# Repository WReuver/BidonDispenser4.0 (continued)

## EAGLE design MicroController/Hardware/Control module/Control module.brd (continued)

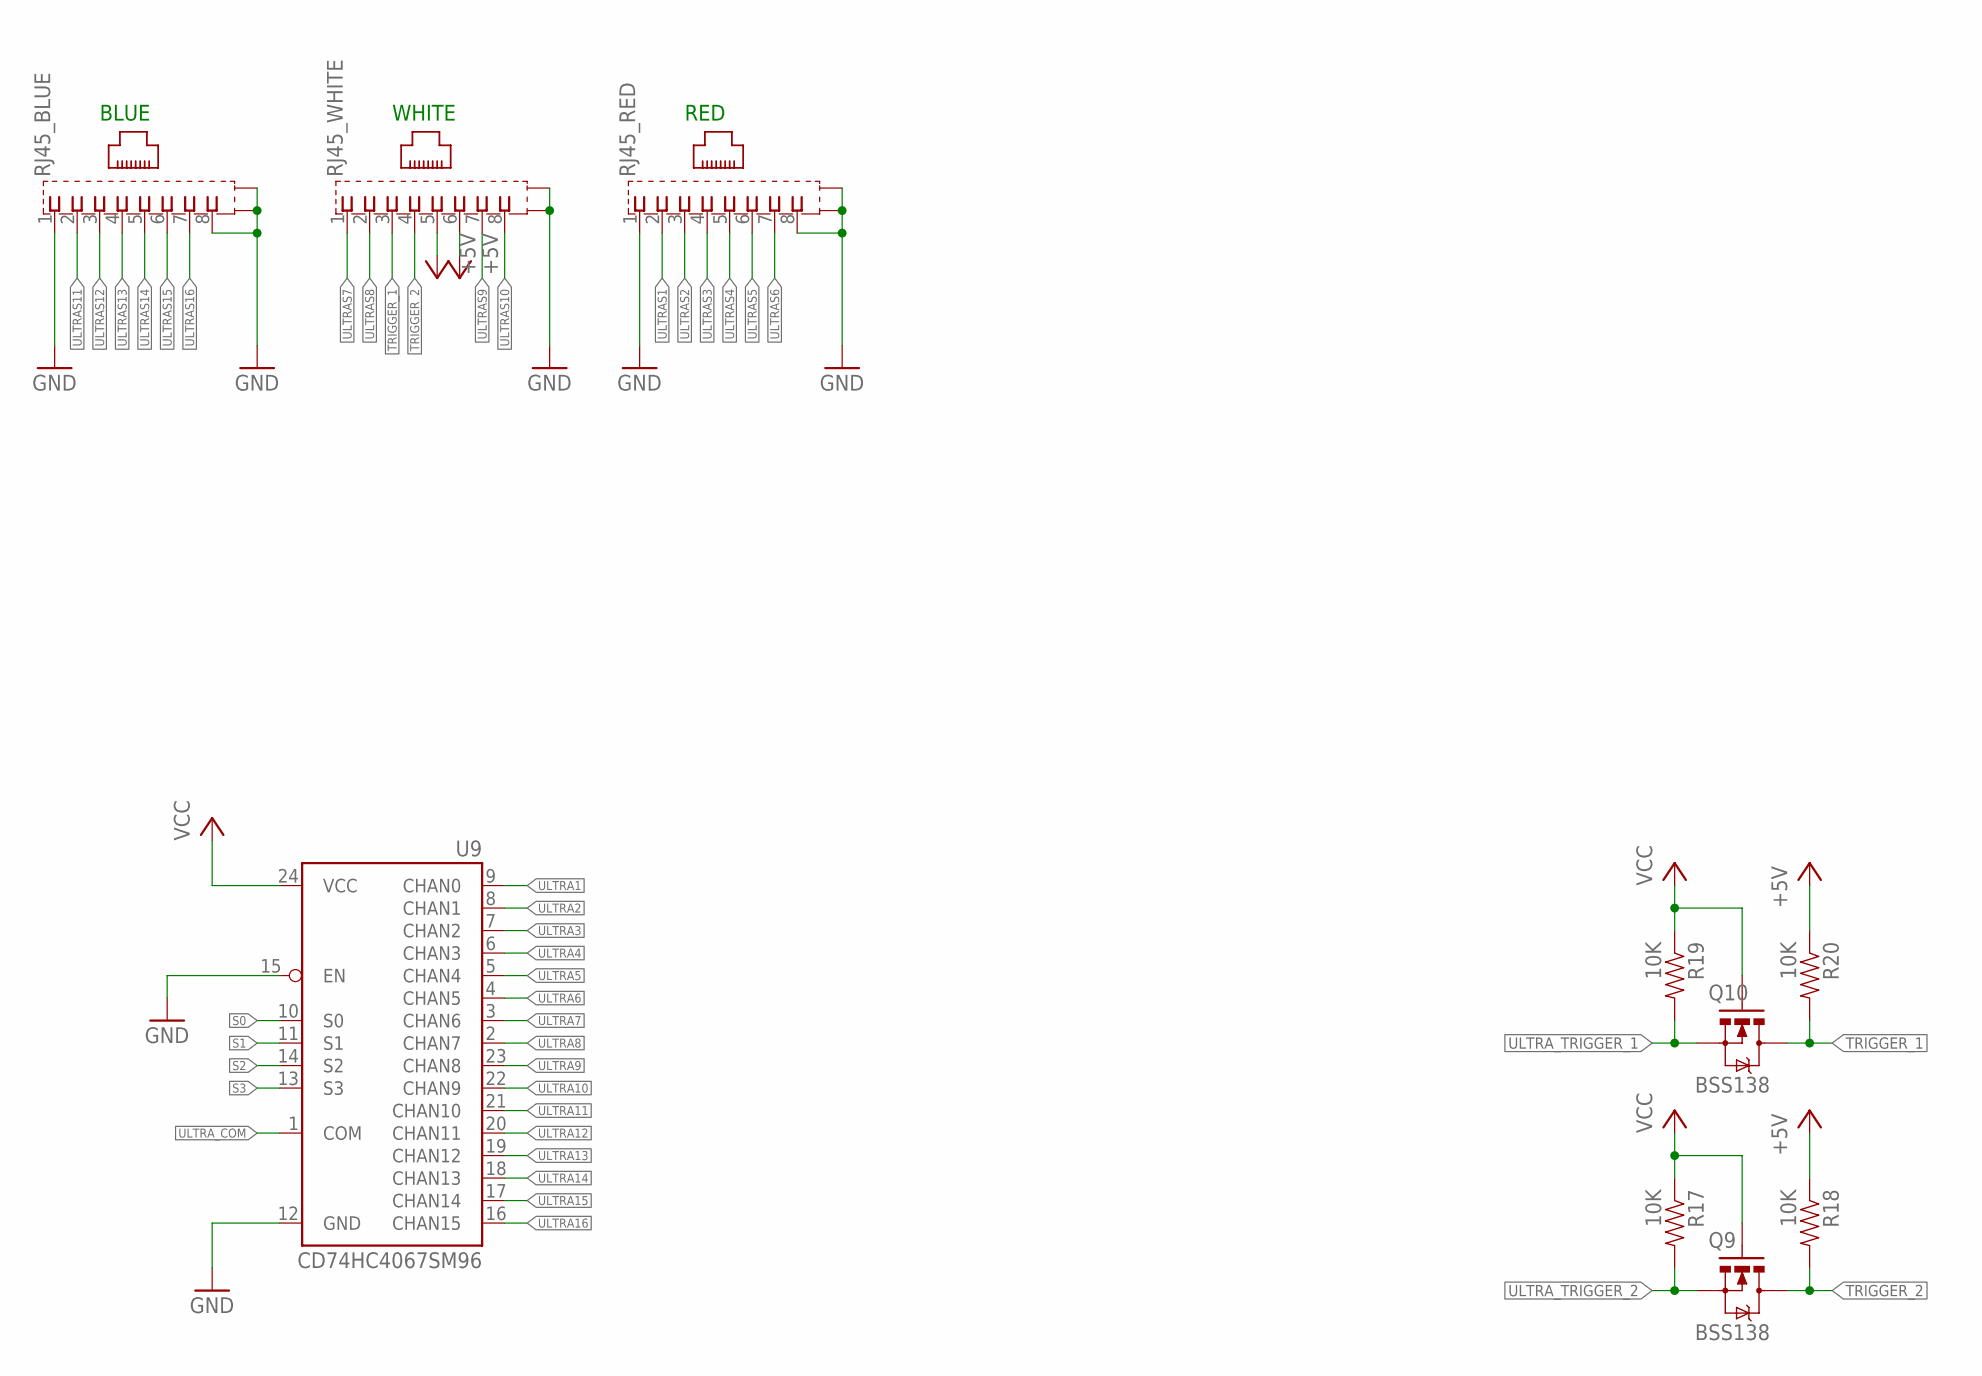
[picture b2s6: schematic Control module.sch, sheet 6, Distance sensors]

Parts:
Q9, Q10: BSS138; SOT23-3
R17, R18, R19, R20: 10K; 0603-RES
RJ45_BLUE, RJ45_RED, RJ45_WHITE: 0446200002
U9: CD74HC4067SM96; SSOP24

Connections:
+5V: R18.1, R20.1, RJ45_WHITE.5, RJ45_WHITE.6; also elsewhere on the board
GND: RJ45_BLUE.1, RJ45_BLUE.8, RJ45_BLUE.S@1 (S1), RJ45_BLUE.S@2 (S2), RJ45_RED.1, RJ45_RED.8, RJ45_RED.S@1 (S1), RJ45_RED.S@2 (S2), RJ45_WHITE.S@1 (S1), RJ45_WHITE.S@2 (S2), U9.12 (GND), U9.15 (EN); also elsewhere on the board
S0: U9.10 (S0); also elsewhere on the board
S1: U9.11 (S1); also elsewhere on the board
S2: U9.14 (S2); also elsewhere on the board
S3: U9.13 (S3); also elsewhere on the board
TRIGGER_1: Q10.3 (D), R20.2, RJ45_WHITE.3
TRIGGER_2: Q9.3 (D), R18.2, RJ45_WHITE.4
ULTRA1: U9.9 (CHAN0); also elsewhere on the board
ULTRA2: U9.8 (CHAN1); also elsewhere on the board
ULTRA3: U9.7 (CHAN2); also elsewhere on the board
ULTRA4: U9.6 (CHAN3); also elsewhere on the board
ULTRA5: U9.5 (CHAN4); also elsewhere on the board
ULTRA6: U9.4 (CHAN5); also elsewhere on the board
ULTRA7: U9.3 (CHAN6); also elsewhere on the board
ULTRA8: U9.2 (CHAN7); also elsewhere on the board
ULTRA9: U9.23 (CHAN8); also elsewhere on the board
ULTRA10: U9.22 (CHAN9); also elsewhere on the board
ULTRA11: U9.21 (CHAN10); also elsewhere on the board
ULTRA12: U9.20 (CHAN11); also elsewhere on the board
ULTRA13: U9.19 (CHAN12); also elsewhere on the board
ULTRA14: U9.18 (CHAN13); also elsewhere on the board
ULTRA15: U9.17 (CHAN14); also elsewhere on the board
ULTRA16: U9.16 (CHAN15); also elsewhere on the board
ULTRAS1: RJ45_RED.2; also elsewhere on the board
ULTRAS2: RJ45_RED.3; also elsewhere on the board
ULTRAS3: RJ45_RED.4; also elsewhere on the board
ULTRAS4: RJ45_RED.5; also elsewhere on the board
ULTRAS5: RJ45_RED.6; also elsewhere on the board
ULTRAS6: RJ45_RED.7; also elsewhere on the board
ULTRAS7: RJ45_WHITE.1; also elsewhere on the board
ULTRAS8: RJ45_WHITE.2; also elsewhere on the board
ULTRAS9: RJ45_WHITE.7; also elsewhere on the board
ULTRAS10: RJ45_WHITE.8; also elsewhere on the board
ULTRAS11: RJ45_BLUE.2; also elsewhere on the board
ULTRAS12: RJ45_BLUE.3; also elsewhere on the board
ULTRAS13: RJ45_BLUE.4; also elsewhere on the board
ULTRAS14: RJ45_BLUE.5; also elsewhere on the board
ULTRAS15: RJ45_BLUE.6; also elsewhere on the board
ULTRAS16: RJ45_BLUE.7; also elsewhere on the board
ULTRA_COM: U9.1 (COM); also elsewhere on the board
ULTRA_TRIGGER_1: Q10.2 (S), R19.2; also elsewhere on the board
ULTRA_TRIGGER_2: Q9.2 (S), R17.2; also elsewhere on the board
VCC: Q9.1 (G), Q10.1 (G), R17.1, R19.1, U9.24 (VCC); also elsewhere on the board

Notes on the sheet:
BLUE
WHITE
RED

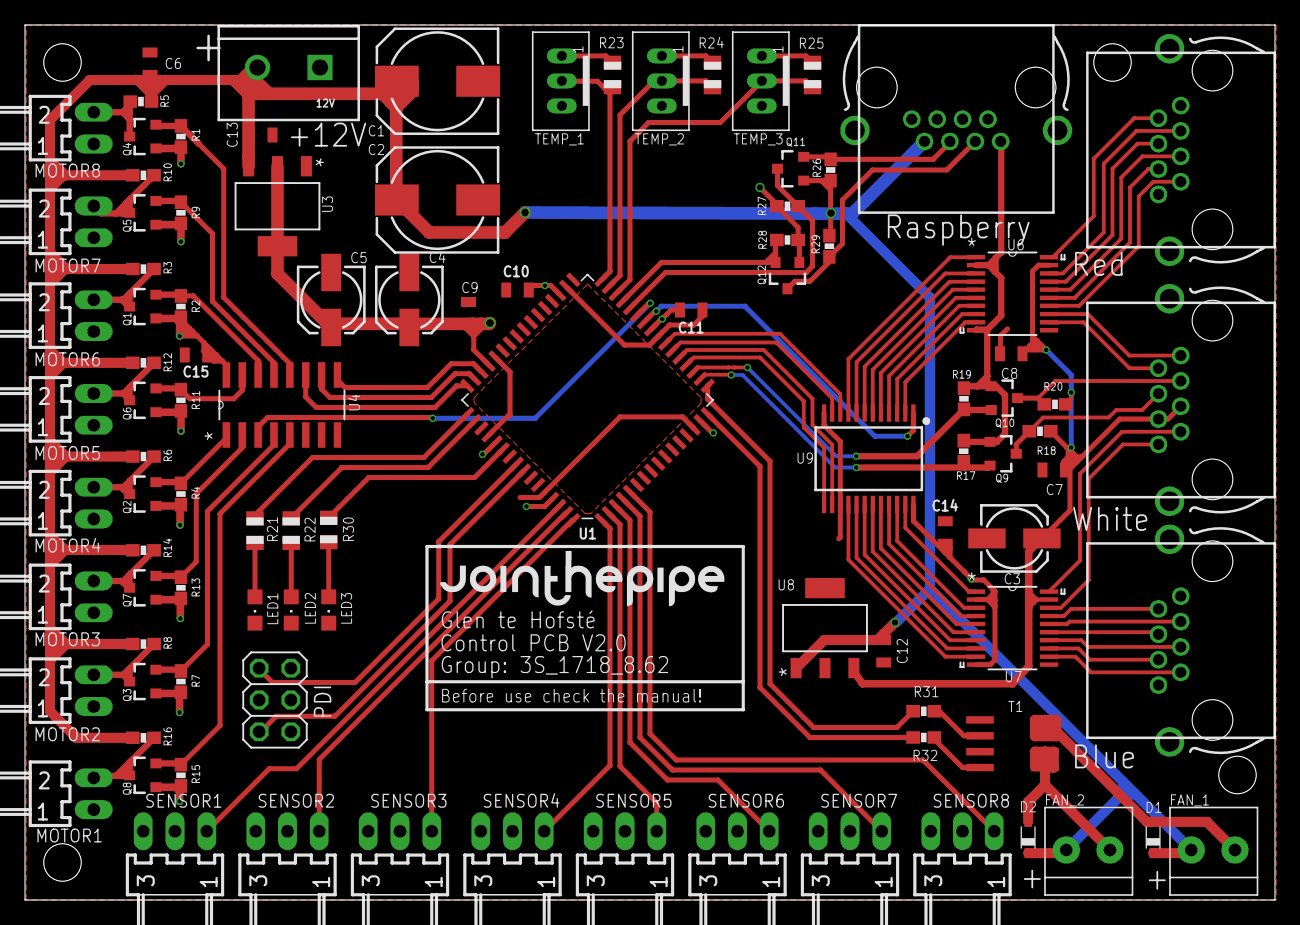
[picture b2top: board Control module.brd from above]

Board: 2 copper layers, 100.0 x 70.0 mm, 99 parts (0 on the bottom side), 94 nets.

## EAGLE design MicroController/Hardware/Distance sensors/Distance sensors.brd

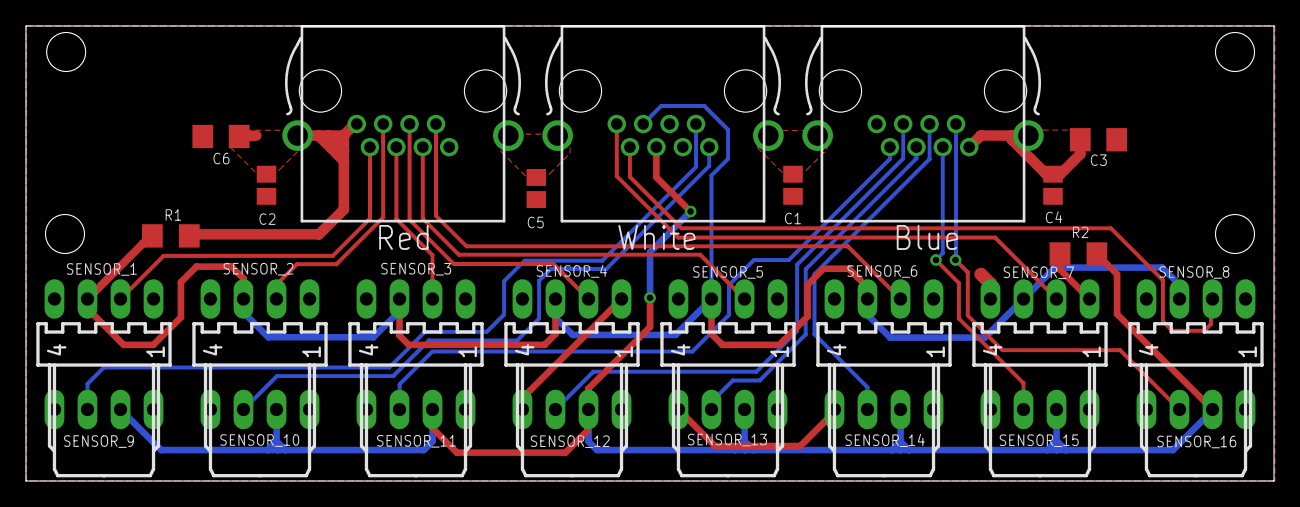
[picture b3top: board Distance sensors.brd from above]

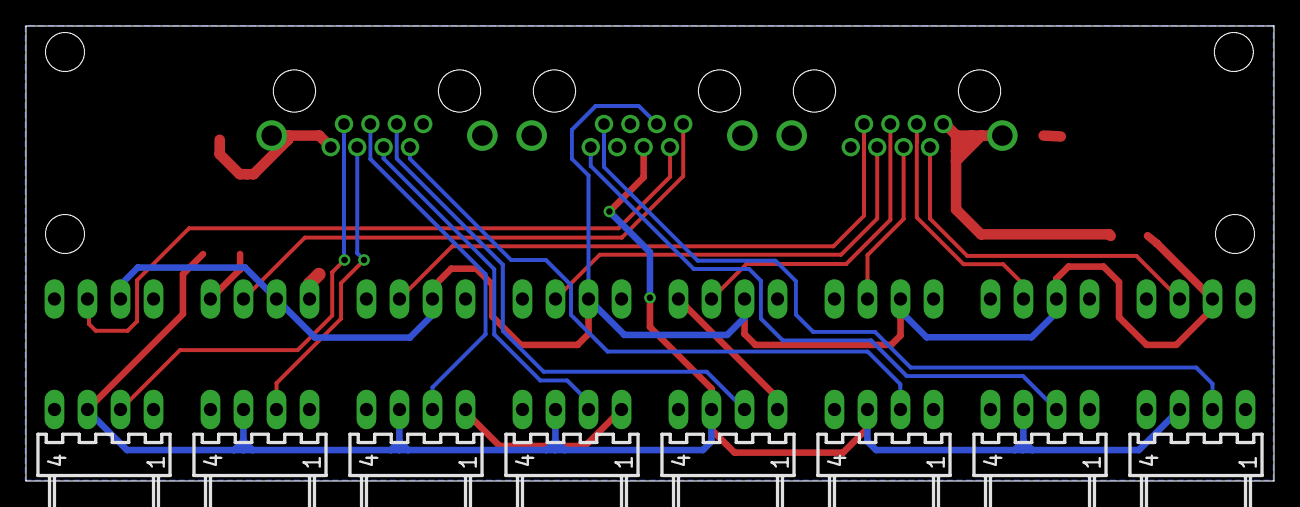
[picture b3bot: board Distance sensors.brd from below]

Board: 2 copper layers, 96.0 x 35.0 mm, 27 parts (8 on the bottom side), 20 nets.

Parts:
C1, C2, C4, C5: C0805
C3, C6: C1206
R1, R2: R1206
SENSOR_1, SENSOR_2, SENSOR_3, SENSOR_4, SENSOR_5, SENSOR_6, SENSOR_7, SENSOR_8, SENSOR_9, SENSOR_10, SENSOR_11, SENSOR_12, SENSOR_13, SENSOR_14, SENSOR_15, SENSOR_16: 22-05-7048-04; 7395-04
X1, X2, X3: 0446200002

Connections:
+5V: C1.1, C2.1, C3.1, C4.1, C5.1, C6.1, SENSOR_1.4, SENSOR_2.4, SENSOR_3.4, SENSOR_4.4, SENSOR_5.4, SENSOR_6.4, SENSOR_7.4, SENSOR_8.4, SENSOR_9.4, SENSOR_10.4, SENSOR_11.4, SENSOR_12.4, SENSOR_13.4, SENSOR_14.4, SENSOR_15.4, SENSOR_16.4, X2.5, X2.6
GND: C1.2, C2.2, C3.2, C4.2, C5.2, C6.2, R1.1, R2.1, SENSOR_1.1, SENSOR_2.1, SENSOR_3.1, SENSOR_4.1, SENSOR_5.1, SENSOR_6.1, SENSOR_7.1, SENSOR_8.1, SENSOR_9.1, SENSOR_10.1, SENSOR_11.1, SENSOR_12.1, SENSOR_13.1, SENSOR_14.1, SENSOR_15.1, SENSOR_16.1, X1.1, X1.8, X1.S@1, X1.S@2, X2.S@1, X2.S@2, X3.1, X3.8, X3.S@1, X3.S@2
TRIGGER_1: R1.2, SENSOR_1.3, SENSOR_2.3, SENSOR_3.3, SENSOR_4.3, SENSOR_5.3, SENSOR_6.3, SENSOR_7.3, SENSOR_8.3, X2.3
TRIGGER_2: R2.2, SENSOR_9.3, SENSOR_10.3, SENSOR_11.3, SENSOR_12.3, SENSOR_13.3, SENSOR_14.3, SENSOR_15.3, SENSOR_16.3, X2.4
ULTRA1: SENSOR_1.2, X1.2
ULTRA2: SENSOR_2.2, X1.3
ULTRA3: SENSOR_3.2, X1.4
ULTRA4: SENSOR_4.2, X1.5
ULTRA5: SENSOR_5.2, X1.6
ULTRA6: SENSOR_6.2, X1.7
ULTRA7: SENSOR_7.2, X2.1
ULTRA8: SENSOR_8.2, X2.2
ULTRA9: SENSOR_9.2, X2.7
ULTRA10: SENSOR_10.2, X2.8
ULTRA11: SENSOR_11.2, X3.2
ULTRA12: SENSOR_12.2, X3.3
ULTRA13: SENSOR_13.2, X3.4
ULTRA14: SENSOR_14.2, X3.5
ULTRA15: SENSOR_15.2, X3.6
ULTRA16: SENSOR_16.2, X3.7

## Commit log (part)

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2018-03-06 Initial commit with an empty gitignore.
2018-03-06 Initial commit.
2018-03-06 The base project.
2018-03-06 Added a gitignore for the project.
2018-03-06 Some basic stuff, blinking a LED etc.
2018-03-09 Started a clean project for the control module
    This module will consists of the microcontroller and all the necessary components needed to make this board function as a proper control module. This module will in the final result communicate with 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
2018-03-12 Added level shifting logic
    The stepper motor drivers require a larger voltage than the microcontroller can deliver. For redundancy this voltage will be higher than 5 volts.
2018-03-12 Created a board file
    This will be the design of the PCB.
2018-03-13 Power regulation implemented on the board design
2018-03-14 Removed some power lines and added the IR sensor connectors
2018-03-15 Looked into motor drivers and changed some components
2018-03-19 Added all the classes I have added in the UML diagram. I still need to think about what the best way is to control all the IO.
2018-03-20 Added the Gpio class to simplify the manipulation of the ports. Changed the main.cpp to a simple blink demo that uses the new Gpio class.
2018-03-22 Changed many things in the layout.
    Added more I/O and connectivity to the Raspberry Pi.
2018-03-22 Filled in the left over empty functions of the SystemClock class. Also wrote the code in the main which still needs to be tested.
2018-03-23 Tested the previous changes, they worked fine.
2018-03-26 Communication line uses optocouplers for signal seperation.
2018-03-26 New project for the ultrasone sensor PCB.
2018-03-26 Added the necessary components for the Distance sensor shield.
2018-03-28 Major improvements
    The Ultrasone PCB is in a good place now, it has also been well implemented on the control PCB.
2018-03-29 Changed the Control PCB design to follow the Eurocircuits design rules.
2018-04-03 Change of plans, instead of Raspbian we wil be running Windows 10 IoT Core on the Raspberry Pi. This means an UWP app will have to be written instead of a javafx app.
    Changes:
    Added the base project for the UWP app.
2018-04-03 Created a small example program. Added a gitignore for the UWP app.
2018-04-03 Added the temperature sensors
    Also changed a lot of connections and PCB traces.
2018-04-04 Got the DS18S20 working, hooray! I've also created an OneWire class to move all the one wire code to in the future. The Temperature sensor specific code will be moved to the "TemperatureSensor" class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
2018-04-06 Finished the TemperatureSensor Class. Changed a few things about the abstract class called "Sensor".
2018-04-06 Added the hardware that makes the TTL line of a higher voltage.
2018-04-09 Changed some minor things to make the PCB less expensive to produce.
    Also the RX TX is now of a higher voltage. This should make the communication less susceptible to noise.
2018-04-10 Added the TimerCounter Class. Past this point the (little amount of) support for the Timer/Counter 2 will be dropped since we do not need it.
2018-04-10 The version that is ordered at Eurocircuits.
    The full version of the microcontroller PCB, revision 1.
2018-04-11 Started a redesign of the Distance sensor PCB.
2018-04-13 Tested the Distance Sensors succesfully.
2018-04-13 Many changes to the Ultrasone sensor PCB.
    Added a lot op components.
2018-04-13 Started to work on some code for the Usart.
2018-04-16 Version with two 5V terminals.
2018-04-17 Changed to one 4-pin connector for each sensor.
2018-04-18 Finished the first version of the Ultrasone PCB.
2018-04-18 Finished the first version of the Ultrasonic PCB.
2018-04-18 Finished the Usart class. Added the GenericTC class, the generic TC will be used for simple temporary timing things. Moved the "new" and "delete" functions. Edited the includes class.
2018-04-19 Added some necessary components for powering the Raspberry.
2018-04-23 Started working on the next revision of the Control PCB.
    Work in progress. The notes on the hardware can be found in the documentation.
2018-04-26 Control PCB revision 2 is now complete.
    A lot of changes compared to the first revision. Most noticable the layout of the connectors and the addition of the motor driver.
2018-05-07 Moved the LED connection to another pin.
2018-05-08 The distance sensor PCB is close to finished.
    There needs to be a final check before ordering the PCB. The PCB is not very complicated compared to the previous version, making it easier to check.
2018-05-14 Added a step up converter.
    This step up is required for the 12 volt data communication between the Raspberry and the microcontroller. It ofcourse also works with the lower 5 volt, but for reliability we use 12 volt.
2018-05-16 Build a small demo to test the GPIO of the Pi. Edited the interface to show a few images which will be used to promote Join the Pipe.
2018-05-16 Many changes to the PCB design.
    Most of the required components have now been included.
2018-05-17 Added a connector for the reed switch.
    The reed switch is used to detect if the door is open. It works in combination with a magnet that is placed on the case itself.
2018-05-17 Finished the first version of the Raspberry PCB.
    Design rule check worked out fine. The PCB should now be ready for ordering.
2018-05-22 The Raspberry PCB is almost finished now.
    The buttons and the jumper has been included. The size has been increased. All the primary functionality has been finished now.
2018-05-22 Worked on the Raspberry Pi class. Added the includes and namespace names in the Cooling Controller class. At last, wrote out the protocol for the usart connection between the microcontroller and the 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
2018-05-23 Cleaned up the MainPage.xaml.cs. Added some code to test the Serial port of the raspberry pi.
2018-05-23 Added information to the soldermask.
2018-05-23 Added the microcontroller class and started filling it in. Wrote some test code for the microcontroller.
2018-05-24 Worked a bit on the UI, not much more really.
2018-05-25 Fixed a few bugs in the microcontroller code. Added an example of how to use the "Raspberry Pi" class.
    Commented out the gif for now, showing it costed a lttle bit too much CPU power to my liking, it also slowed down the promotion timer somehow.
    Changed the UI a bit, added some button for command testing to the microcontroller.
    Removed some old Serial test code.
    Finished the "Microcontroller" class.
2018-05-25 Added some more images. Reordered the layout of the "Assets" folder.
2018-05-27 Generated all the asset images. Edited the Serial test code a bit. Worked a bit on the different UI Panels.
2018-05-28 Finished the UI. Added some code for the buttons, now the user can interact with the program using the buttons. Cleaned up the code a bit as well.
2018-05-28 Added some values to the components.
    These are handy when generating the BOM file.
2018-05-30 Continued working on the main routine of the program. Changed the working of the rotation sensor class a bit, one instance of this class now represents all eight rotation sensors. Updated the communi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
2018-05-30 Started on removing the sensor class. Also updated the distance sensor class a bit to work correctly with the system.
2018-05-31 Tested the motorcontroller, it works! Replaced the ledcontroller with functions in the main. Some minor changes in the distance sensor.
2018-05-31 Added a few comments.
2018-05-31 Added some more comments here and there. Filled in most of the coolingcontroller class except for the "updateFanSpeed" method. Fixed a small bug in the motorcontroller where it would always pick the 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
2018-06-04 Tested some software spi code for the pn532.
2018-06-04 One of the rotation sensor's pins somehow could not notice when it was high, this is why we've used the ADC to check their status. Wrote some more code for the cooling controller.
2018-06-05 Nothing has changed that's worth mentioning.
2018-06-05 Tested the distance sensors with the final setup. Changed the order of the distance sensors so their "echo" signals won't get mixed.
2018-06-05 Some more testing with the fans.
2018-06-06 Started on implementing a Mutex so the serial port won't be spammed with data. Added the door sensor and timers to the "unloadMainPage" function so everything will be cleaned up nicely when the progr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
2018-06-06 Added a few methods to the cooling controller class for testing purposes. Fixed a pretty embarrassing bug in the onewire class. Added a temperature test function in the main.
2018-06-07 Updated the protocol specification. Changed the "Temperature check" command to the "temperature" command, this command will return the three temperatures in the machine. Cleaned up the test functions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
2018-06-08 Worked a bit on improving the way commands get executed.
2018-06-08 The command processing on the microcontroller works fine!
2018-06-11 Wrote a small program which logs the temperature data of the microcontroller. Turned the animation for the progressbar on. Added the lower temperature variable to the main model. Added some more usef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
2018-06-11 Many changes in this new version of the Control PCB.
    The motor drivers are replaced by MOSFET's.
    The schematic is much better organized.
    Small additional changes.
2018-06-12 Finished the Control PCB version 2.0
    Not a lot of changes where made comparing to the previous version of the PCB. Most noticeably the way the fans are controlled has changed. Further some small things that where found out during tests 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
2018-06-13 Updated the readme.
    Some minor changes in the microcontroller's code.
    Change the lowerbottle's temperature type to a double instead of an int.
    Added a test panel to the ui for the mechanical engineering boiis.
    Added some code which cooperates with the mechanical engineering test ui.
    Edited the "sendDispenseCommand" method.
2018-06-14 Added a lot more images. Some other minor changes.
2018-06-18 Worked some more on the general workings of the software.
2018-06-19 Added a bunch of comments to the main, you're welcome. Changed the "Sense" command to also work when the micro controller is locked.
2018-06-20 Added some error screens and a very secret easter egg... huh?
2018-06-21 Changed some of the pins for the micro controller PCB v2.0.
2018-06-22 Fixed a pretty embarrassing bug in the Gpio class. Updated the protocol description. Made the lower target temperature configurable again. Removed the ugly ADC code from the motorController and repla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
2018-06-25 Updated the code to be able to control the fans again.
2018-06-25 The maintenance timer now executes the "temperature" command. The process of updating the UI when a column is empty has been streamlined. Added the "isBottleAvailable" method in the MainModel. Moved 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
2018-06-25 Tried to remove the semaphores.
2018-06-26 Kept the semaphore. Added a palce for the lower bottle temperature. Added some pictures for the lower bottle temperature.
2018-06-27 Changed a few things about how text is logged.
2018-06-27 Revert "Replaced the semaphore with a simple boolean."
    This reverts commit c06132580691cdc1e07f443547ccae97d792c913.
2018-06-27 Changed one error message.
2018-06-27 Updated the README with some more information.
2018-06-27 Updated the readme (again).
2018-06-27 Lowered the resolution of the team photo. Updated the readme.
2018-06-27 Updated the readme again again.
2018-06-28 Cleaned up the code. Added a lot of comments. Removed the "HelloViewModel" class. Updated the temperature command in the code and protocol description. Made the pn532 classes "obsolete", but did not 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
2018-10-11 commented out three broken ultra sonic sensors from the loop
